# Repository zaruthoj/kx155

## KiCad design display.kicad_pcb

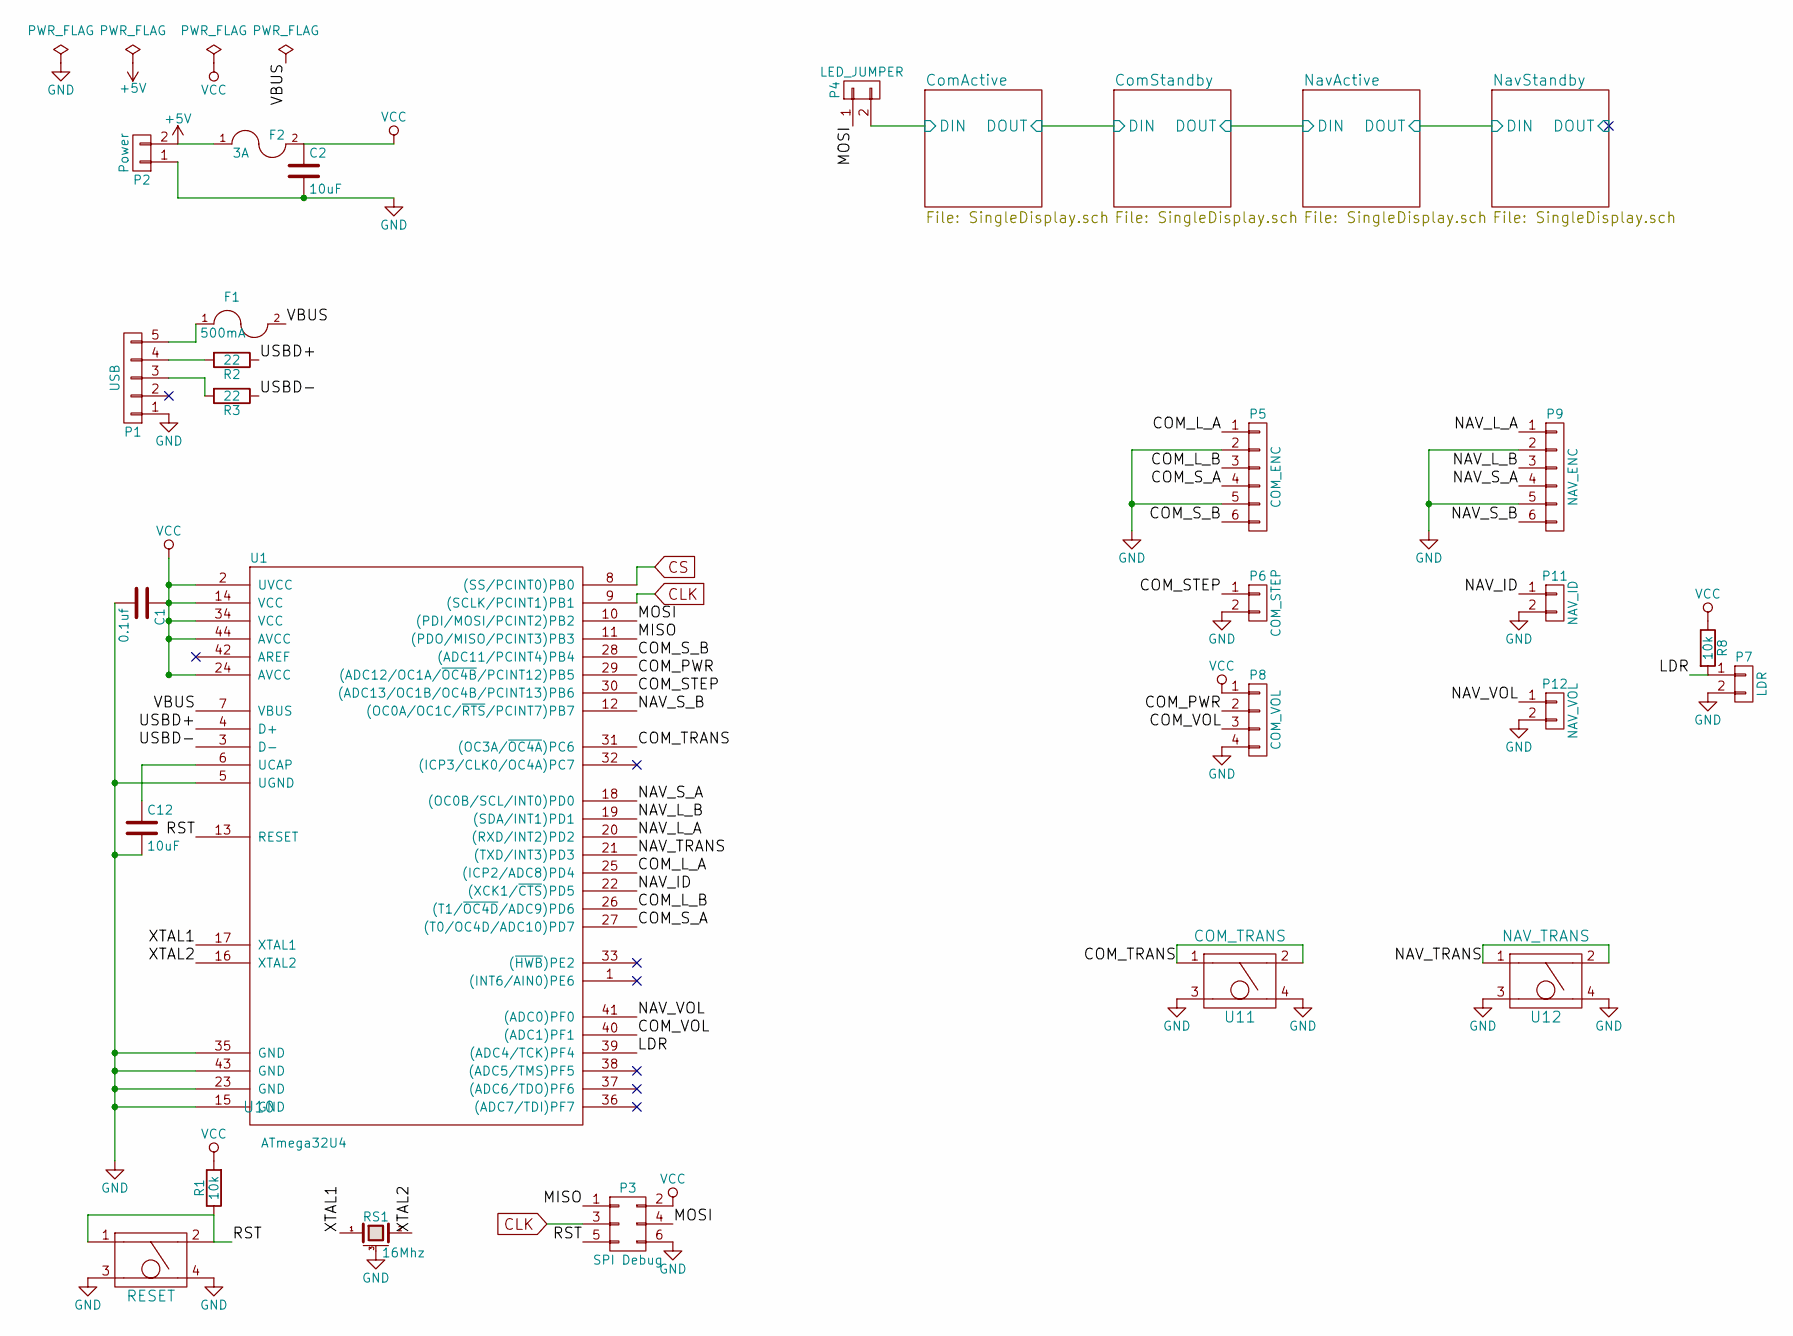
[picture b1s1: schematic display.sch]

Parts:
C1: 0.1uf; C_0805
C2, C12: 10uF; C_0805
F1: 500mA; R_0805
F2: 3A; R_0805
P1: USB; JST-ZH-THRx5
P2: Power; Pin_Header_Straight_1x02_Pitch2.54mm
P3: SPI Debug; Pin_Header_Straight_2x03_Pitch2.54mm
P4: LED_JUMPER; Pin_Header_Straight_1x02_Pitch2.54mm
P5: COM_ENC; JST-ZH-THRx6
P6: COM_STEP; JST-ZH-THRx2
P7: LDR; JST-ZH-THRx2
P8: COM_VOL; JST-ZH-THRx4
P9: NAV_ENC; JST-ZH-THRx6
P11: NAV_ID; JST-ZH-THRx2
P12: NAV_VOL; JST-ZH-THRx2
R1, R8: 10k; R_0805
R2, R3: 22; R_0805
RS1: 16Mhz; RESONATOR_SMD_Abracon_AWSCR
U1: ATmega32U4; TQFP-44_10x10mm_Pitch0.8mm
U10: RESET; TAC_SWITCH_PTS645_SMD
U11: COM_TRANS; TAC_SWITCH_CK_KSC4_JWING
U12: NAV_TRANS; TAC_SWITCH_CK_KSC4_JWING

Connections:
+5V: F2.1, P2.2
/COM_L_A: P5.1, U1.25 ((ICP2/ADC8)PD4)
/COM_L_B: P5.3, U1.26 ((T1/~OC4D~/ADC9)PD6)
/COM_PWR: P8.2, U1.29 ((ADC12/OC1A/~OC4B~/PCINT12)PB5)
/COM_STEP: P6.1, U1.30 ((ADC13/OC1B/OC4B/PCINT13)PB6)
/COM_S_A: P5.4, U1.27 ((T0/OC4D/ADC10)PD7)
/COM_S_B: P5.6, U1.28 ((ADC11/PCINT4)PB4)
/COM_TRANS: U1.31 ((OC3A/~OC4A~)PC6), U11.1, U11.2
/COM_VOL: P8.3, U1.40 ((ADC1)PF1)
/ComActive/DIN: P4.2; also elsewhere on the board
/LDR: P7.1, R8.2, U1.39 ((ADC4/TCK)PF4)
/MISO: P3.1, U1.11 ((PDO/MISO/PCINT3)PB3)
/MOSI: P3.4, P4.1, U1.10 ((PDI/MOSI/PCINT2)PB2)
/NAV_ID: P11.1, U1.22 ((XCK1/~CTS~)PD5)
/NAV_L_A: P9.1, U1.20 ((RXD/INT2)PD2)
/NAV_L_B: P9.3, U1.19 ((SDA/INT1)PD1)
/NAV_S_A: P9.4, U1.18 ((OC0B/SCL/INT0)PD0)
/NAV_S_B: P9.6, U1.12 ((OC0A/OC1C/~RTS~/PCINT7)PB7)
/NAV_TRANS: U1.21 ((TXD/INT3)PD3), U12.1, U12.2
/NAV_VOL: P12.1, U1.41 ((ADC0)PF0)
/RST: P3.5, R1.1, U1.13 (RESET), U10.1, U10.2
/USBD+: R2.1, U1.4 (D+)
/USBD-: R3.1, U1.3 (D-)
/VBUS: F1.2, U1.7 (VBUS)
/XTAL1: RS1.1, U1.17 (XTAL1)
/XTAL2: RS1.2, U1.16 (XTAL2)
CLK: P3.3, U1.9 ((SCLK/PCINT1)PB1); also elsewhere on the board
CS: U1.8 ((SS/PCINT0)PB0); also elsewhere on the board
GND: C1.2, C2.2, C12.2, P1.1, P2.1, P3.6, P5.2, P5.5, P6.2, P7.2, P8.4, P9.2, P9.5, P11.2, P12.2, RS1.3 (case), U1.5 (UGND), U1.15 (GND), U1.23 (GND), U1.35 (GND), U1.43 (GND), U10.3, U10.4, U11.3, U11.4, U12.3, U12.4; also elsewhere on the board
unnamed: C12.1, U1.6 (UCAP)
unnamed: F1.1, P1.5
unnamed: P1.3, R3.2
unnamed: P1.4, R2.2
VCC: C1.1, C2.1, F2.2, P3.2, P8.1, R1.2, R8.1, U1.2 (UVCC), U1.14 (VCC), U1.24 (AVCC), U1.34 (VCC), U1.44 (AVCC); also elsewhere on the board

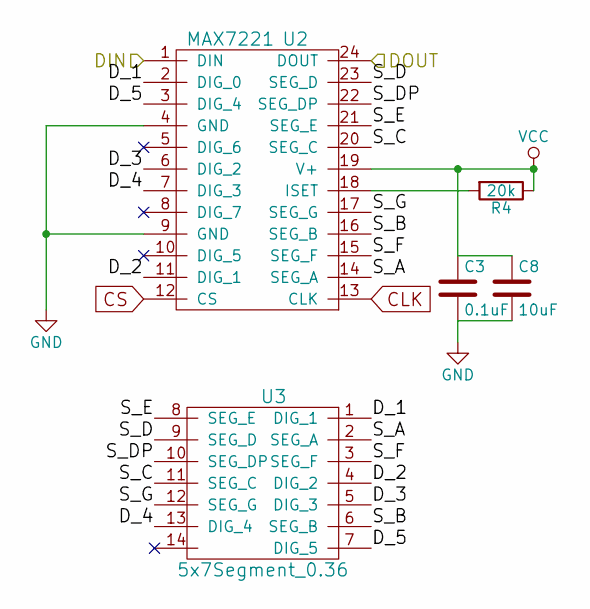
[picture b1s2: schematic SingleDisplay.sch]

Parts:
C3: 0.1uF; C_0805
C8: 10uF; C_0805
R4: 20k; R_0805
U2: MAX7221; MAX7221CWG
U3: 5x7Segment_0.36

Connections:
/ComActive/DIN: U2.1 (DIN); also elsewhere on the board
/ComActive/D_1: U2.2 (DIG_0), U3.1 (DIG_1)
/ComActive/D_2: U2.11 (DIG_1), U3.4 (DIG_2)
/ComActive/D_3: U2.6 (DIG_2), U3.5 (DIG_3)
/ComActive/D_4: U2.7 (DIG_3), U3.13 (DIG_4)
/ComActive/D_5: U2.3 (DIG_4), U3.7 (DIG_5)
/ComActive/S_A: U2.14 (SEG_A), U3.2 (SEG_A)
/ComActive/S_B: U2.16 (SEG_B), U3.6 (SEG_B)
/ComActive/S_C: U2.20 (SEG_C), U3.11 (SEG_C)
/ComActive/S_D: U2.23 (SEG_D), U3.9 (SEG_D)
/ComActive/S_DP: U2.22 (SEG_DP), U3.10 (SEG_DP)
/ComActive/S_E: U2.21 (SEG_E), U3.8 (SEG_E)
/ComActive/S_F: U2.15 (SEG_F), U3.3 (SEG_F)
/ComActive/S_G: U2.17 (SEG_G), U3.12 (SEG_G)
/ComStandby/DIN: U2.24 (DOUT); also elsewhere on the board
CLK: U2.13 (CLK); also elsewhere on the board
CS: U2.12 (CS); also elsewhere on the board
GND: C3.2, C8.2, U2.4 (GND), U2.9 (GND); also elsewhere on the board
unnamed: R4.2, U2.18 (ISET)
VCC: C3.1, C8.1, R4.1, U2.19 (V+); also elsewhere on the board

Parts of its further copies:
C4, C5, C6: 0.1uF; C_0805
C9, C10, C11: 10uF; C_0805
R5, R6, R7: 20k; R_0805
U4, U6, U8: MAX7221; MAX7221CWG
U5, U7, U9: 5x7Segment_0.36

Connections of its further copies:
/ComStandby/DIN: U4.1 (DIN); also elsewhere on the board
/ComStandby/D_1: U4.2 (DIG_0), U5.1 (DIG_1)
/ComStandby/D_2: U4.11 (DIG_1), U5.4 (DIG_2)
/ComStandby/D_3: U4.6 (DIG_2), U5.5 (DIG_3)
/ComStandby/D_4: U4.7 (DIG_3), U5.13 (DIG_4)
/ComStandby/D_5: U4.3 (DIG_4), U5.7 (DIG_5)
/ComStandby/S_A: U4.14 (SEG_A), U5.2 (SEG_A)
/ComStandby/S_B: U4.16 (SEG_B), U5.6 (SEG_B)
/ComStandby/S_C: U4.20 (SEG_C), U5.11 (SEG_C)
/ComStandby/S_D: U4.23 (SEG_D), U5.9 (SEG_D)
/ComStandby/S_DP: U4.22 (SEG_DP), U5.10 (SEG_DP)
/ComStandby/S_E: U4.21 (SEG_E), U5.8 (SEG_E)
/ComStandby/S_F: U4.15 (SEG_F), U5.3 (SEG_F)
/ComStandby/S_G: U4.17 (SEG_G), U5.12 (SEG_G)
/NavActive/DIN: U4.24 (DOUT), U6.1 (DIN)
/NavActive/D_1: U6.2 (DIG_0), U7.1 (DIG_1)
/NavActive/D_2: U6.11 (DIG_1), U7.4 (DIG_2)
/NavActive/D_3: U6.6 (DIG_2), U7.5 (DIG_3)
/NavActive/D_4: U6.7 (DIG_3), U7.13 (DIG_4)
/NavActive/D_5: U6.3 (DIG_4), U7.7 (DIG_5)
/NavActive/S_A: U6.14 (SEG_A), U7.2 (SEG_A)
/NavActive/S_B: U6.16 (SEG_B), U7.6 (SEG_B)
/NavActive/S_C: U6.20 (SEG_C), U7.11 (SEG_C)
/NavActive/S_D: U6.23 (SEG_D), U7.9 (SEG_D)
/NavActive/S_DP: U6.22 (SEG_DP), U7.10 (SEG_DP)
/NavActive/S_E: U6.21 (SEG_E), U7.8 (SEG_E)
/NavActive/S_F: U6.15 (SEG_F), U7.3 (SEG_F)
/NavActive/S_G: U6.17 (SEG_G), U7.12 (SEG_G)
/NavStandby/DIN: U6.24 (DOUT), U8.1 (DIN)
/NavStandby/D_1: U8.2 (DIG_0), U9.1 (DIG_1)
/NavStandby/D_2: U8.11 (DIG_1), U9.4 (DIG_2)
/NavStandby/D_3: U8.6 (DIG_2), U9.5 (DIG_3)
/NavStandby/D_4: U8.7 (DIG_3), U9.13 (DIG_4)
/NavStandby/D_5: U8.3 (DIG_4), U9.7 (DIG_5)
/NavStandby/S_A: U8.14 (SEG_A), U9.2 (SEG_A)
/NavStandby/S_B: U8.16 (SEG_B), U9.6 (SEG_B)
/NavStandby/S_C: U8.20 (SEG_C), U9.11 (SEG_C)
/NavStandby/S_D: U8.23 (SEG_D), U9.9 (SEG_D)
/NavStandby/S_DP: U8.22 (SEG_DP), U9.10 (SEG_DP)
/NavStandby/S_E: U8.21 (SEG_E), U9.8 (SEG_E)
/NavStandby/S_F: U8.15 (SEG_F), U9.3 (SEG_F)
/NavStandby/S_G: U8.17 (SEG_G), U9.12 (SEG_G)
CLK: U4.13 (CLK), U6.13 (CLK), U8.13 (CLK); also elsewhere on the board
CS: U4.12 (CS), U6.12 (CS), U8.12 (CS); also elsewhere on the board
GND: C4.2, C5.2, C6.2, C9.2, C10.2, C11.2, U4.4 (GND), U4.9 (GND), U6.4 (GND), U6.9 (GND), U8.4 (GND), U8.9 (GND); also elsewhere on the board
unnamed: R5.2, U4.18 (ISET)
unnamed: R6.2, U6.18 (ISET)
unnamed: R7.2, U8.18 (ISET)
VCC: C4.1, C5.1, C6.1, C9.1, C10.1, C11.1, R5.1, R6.1, R7.1, U4.19 (V+), U6.19 (V+), U8.19 (V+); also elsewhere on the board

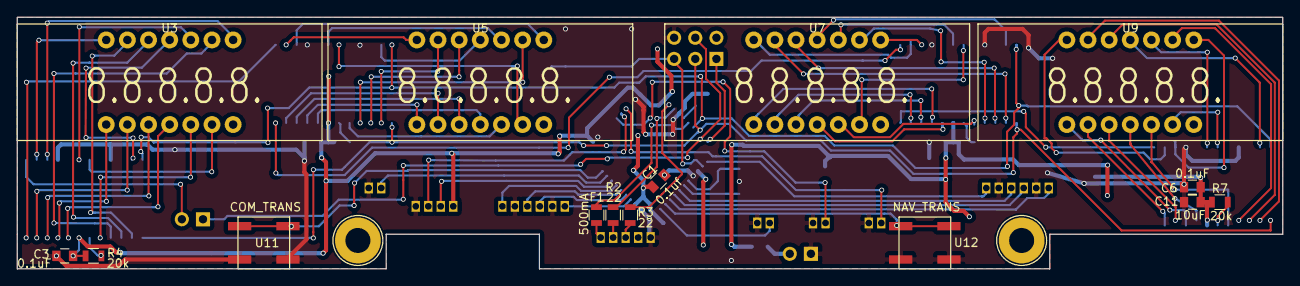
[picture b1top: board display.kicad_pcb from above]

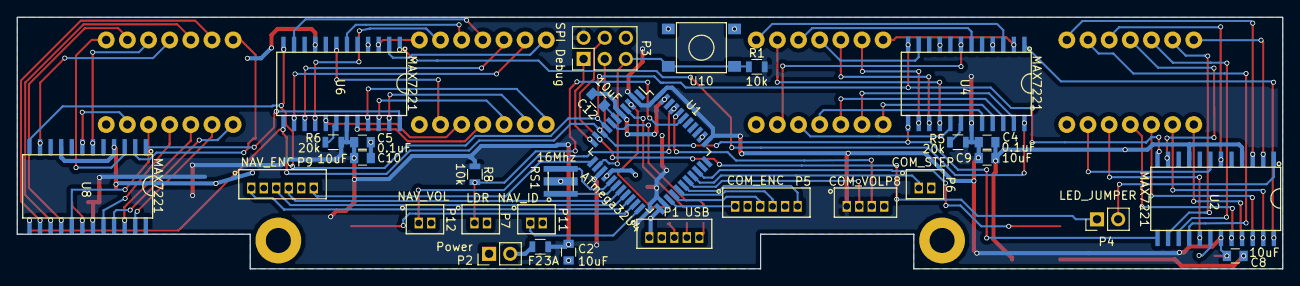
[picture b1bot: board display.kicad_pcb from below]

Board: 2 copper layers, 151.9 x 30.2 mm, 47 parts (30 on the bottom side), 93 nets.

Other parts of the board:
Ref**: Val**; SCREW_4-40
Ref**#2: Val**; SCREW_4-40

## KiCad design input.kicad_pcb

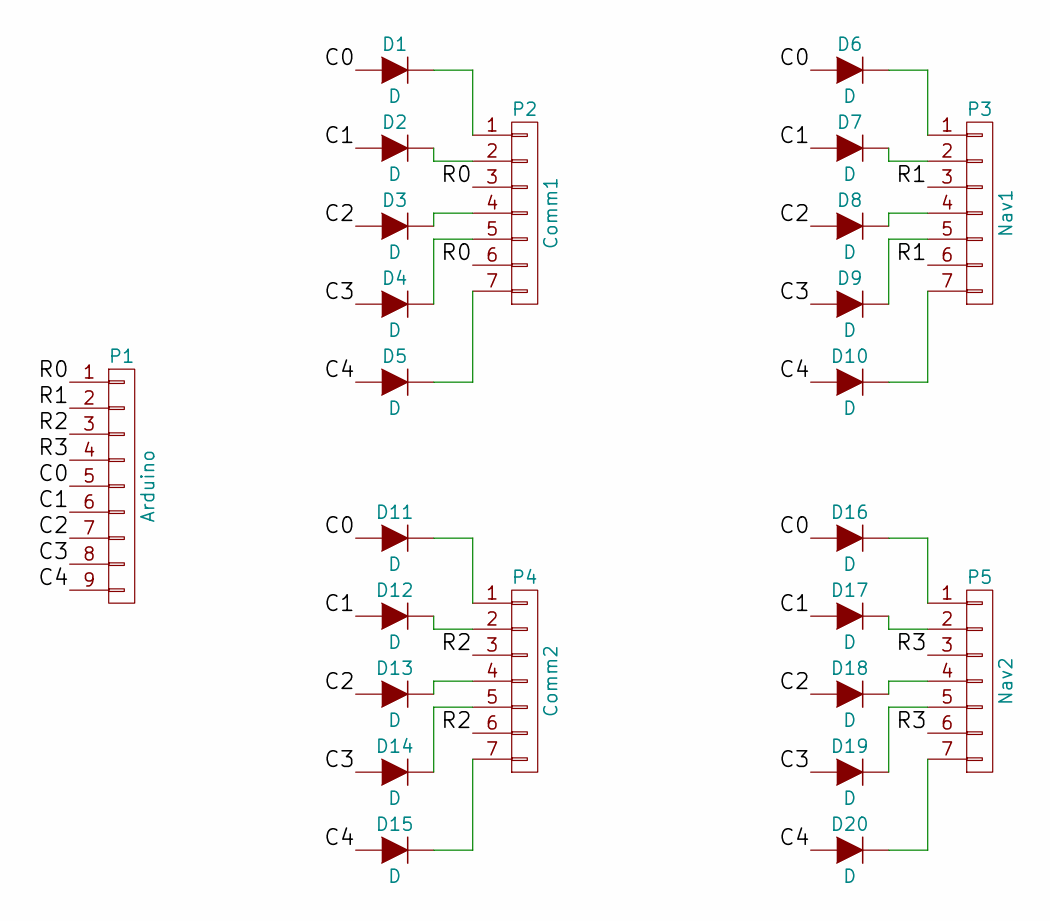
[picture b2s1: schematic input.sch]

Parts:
D1, D2, D3, D4, D5, D6, D7, D8, D9, D10, D11, D12, D13, D14, D15, D16, D17, D18, D19, D20: D; Diode_SMD
P1: Arduino; Pin_Header_Straight_1x09
P2: Comm1; B7B-ZR
P3: Nav1; B7B-ZR
P4: Comm2; B7B-ZR
P5: Nav2; B7B-ZR

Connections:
/C0: D1.2 (A), D6.2 (A), D11.2 (A), D16.2 (A), P1.5
/C1: D2.2 (A), D7.2 (A), D12.2 (A), D17.2 (A), P1.6
/C2: D3.2 (A), D8.2 (A), D13.2 (A), D18.2 (A), P1.7
/C3: D4.2 (A), D9.2 (A), D14.2 (A), D19.2 (A), P1.8
/C4: D5.2 (A), D10.2 (A), D15.2 (A), D20.2 (A), P1.9
/R0: P1.1, P2.3, P2.6
/R1: P1.2, P3.3, P3.6
/R2: P1.3, P4.3, P4.6
/R3: P1.4, P5.3, P5.6
unnamed: D1.1 (K), P2.1
unnamed: D2.1 (K), P2.2
unnamed: D3.1 (K), P2.4
unnamed: D4.1 (K), P2.5
unnamed: D5.1 (K), P2.7
unnamed: D6.1 (K), P3.1
unnamed: D7.1 (K), P3.2
unnamed: D8.1 (K), P3.4
unnamed: D9.1 (K), P3.5
unnamed: D10.1 (K), P3.7
unnamed: D11.1 (K), P4.1
unnamed: D12.1 (K), P4.2
unnamed: D13.1 (K), P4.4
unnamed: D14.1 (K), P4.5
unnamed: D15.1 (K), P4.7
unnamed: D16.1 (K), P5.1
unnamed: D17.1 (K), P5.2
unnamed: D18.1 (K), P5.4
unnamed: D19.1 (K), P5.5
unnamed: D20.1 (K), P5.7

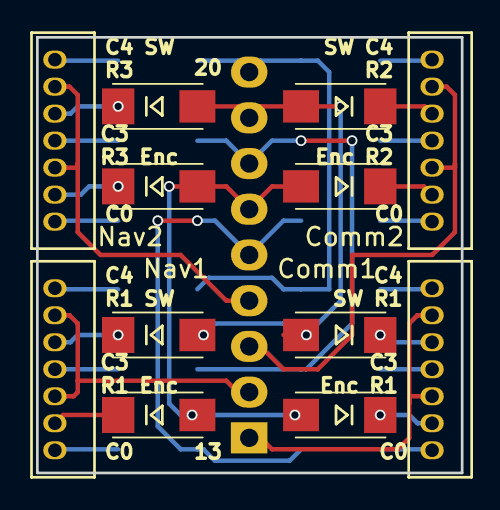
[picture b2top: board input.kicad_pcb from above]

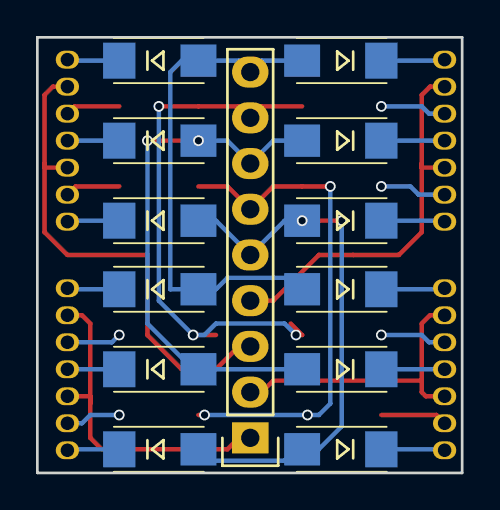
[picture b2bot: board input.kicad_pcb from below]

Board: 2 copper layers, 23.6 x 24.2 mm, 25 parts (13 on the bottom side), 29 nets.

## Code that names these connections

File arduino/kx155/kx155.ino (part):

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
#define POWER 9

#define COM_S_A 6
#define COM_S_B 8
#define COM_L_A 4
#define COM_L_B 12
#define COM_TRANS 5
#define COM_STEP 10
#define COM_VOL 4
#define COM_PRIMARY_LED 0
#define COM_STANDBY_LED 1

#define NAV_S_A 3
#define NAV_S_B 11
#define NAV_L_A 0
#define NAV_L_B 2
#define NAV_TRANS 1
//#define NAV_ID 30 // Does not work since PD5 is assigned as LED TX in Arduino.
//#define NAV_VOL 5 // I built support for nav volume into the PCB but didn't expect to use it since no current sim supports it.  Re-assigning this plug as NAV ID.  Digital pin 23 = PF0 = analog pin 5.
#define NAV_ID 23
#define NAV_PRIMARY_LED 2
#define NAV_STANDBY_LED 3

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
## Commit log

2017-10-18 Create LICENSE
2017-10-23 Finished trace routing. Added 3d parts
2017-10-23 Fixed unconnected ground.
2017-10-23 Added 3d footprints for tac switches and resonator.
2017-10-26 Updated with actual dimensions from 7 segment displays. Deleted unused files.
2017-10-26 Move library to separate project
2018-03-11 Tons of updates. Mostly working.
2018-03-12 All inputs working.
2018-03-12 Add support for syncing KX155 on startup and auto-detecting the com port. Untested.
